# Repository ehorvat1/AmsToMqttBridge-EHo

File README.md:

# AMS2MQTTBridge-EHo
This is basically a fork from amsreader-firmware (old name: AmsToMqttBridge) amsreader-firmware based on Rev 2.2.21 from here: (https://github.com/UtilitechAS/amsreader-firmware)

Because of memory limitations for ESP8266 which made OTA firmware update impossible I had to delete the automatic firmware detection/download/consent. So this firmware can only be updated via status web page (Upload Firmware) or by using direct serial connection to ESP device.

Now features:
1) All functions from amsreader-firmware Rev 2.2.21 (Except automatic FW updates which would overwrite my modifications)
2) Fixed price (but its more a refund) for exported energy 
3) Added a 10 Minute plot (120 point resolution, 1 pt each 5 sec)
4) Added a 60 Minute plot (120 point resolution, 1 pt each 30 sec)
5) Added a section to show "last" counter values since last payment. Data to be entered in configuration.
6) Exported energy is shown in green color on hour, day and month plot.
7) Automatic Wifi swapping if configured WLAN does not connect. See below for more info.
8) Disabled Consent message (since no data is sent anywhere) and automatic FW updates
9) Some minor color changes on dashboard gauges

There is a German Version as well, please go to "main" branch or to the Release version ending with "-ge" . Link: https://github.com/ehorvat1/AmsToMqttBridge-EHo/tree/main

## Wifi function (STA mode or AP mode):
The option on configuration page in section Wifi called:  "Start a Wifi AP on home Wifi connection problem" will enable this:
If the configured Wifi (should be your home Wifi) can not be reached within app. 2 minutes software will swap to Wifi AP mode and will present a AP named "amsreader-abcd" with **password: amsreader_config** so one can acess the web pages on its default IP: 192.168.4.1

Software will try to re-connect to the configured Wifi if no client is connected to this AP for 90 seconds. So if one is connected to AP Wifi the device will stay in AP mode. Please mind that most devices will do a automatic reconnect to the AP Wifi if the Wifi connection "amsreader-abcd" was once used. This could prevent the ESP32 from automatically reconnecting to defined STA Wifi.

"AP" button still is an option to swap between configured WLAN and an Wifi Access point called "amsreader-abcd". The AP button must be pressed longer than 5 seconds to swap Wifi mode.

## Additional MQTT items (in raw MQTT mode only):
	 - Publish topic + "/realtime/import/cost_kwh"
	 - Publish topic + "/realtime/import/last_counter_value"
	 - Publish topic + "/realtime/import/last_counter_info"
	 - Publish topic + "/realtime/import/last_counter_diff"
	 - Publish topic + "/realtime/import/last_counter_costs"
	 - Publish topic + "/realtime/export/refund_kwh"
	 - Publish topic + "/realtime/export/last_counter_value"
	 - Publish topic + "/realtime/export/last_counter_info"
	 - Publish topic + "/realtime/export/last_counter_diff"
	 - Publish topic + "/realtime/export/last_counter_refund"

So for example, if you set the "Publish topic" in MQTT configuration to "smartmeter" :
          -the actual power used is published with full topic: smartmeter/meter/import/active
          -the entered fixed price per kWh is published with full topic: smartmeter/realtime/import/cost_kwh
	  
## Dashboard website:

## Original README.md from amsreader-firmware:

This code is designed to decode data from electric smart meters installed in many countries in Europe these days. The data is presented in a graphical web interface and can also send the data to a MQTT broker which makes it suitable for home automation project. Originally it was only designed to work with Norwegian meters, but has since been adapter to read any IEC-62056-7-5 or IEC-62056-21 compliant meters.

Later development have added Energy usage graph for both day and month, as well as future energy price (Prices only  available for ESP32). The code can run on any ESP8266 or ESP32 hardware which you can read more about in the [WiKi](https://github.com/gskjold/AmsToMqttBridge/wiki). If you don't have the knowledge to set up a ESP device yourself, have a look at the shop at [amsleser.no](https://amsleser.no/).

Go to the [WiKi](https://github.com/gskjold/AmsToMqttBridge/wiki) for information on how to get your own device! And find the latest prebuilt firmware file at the [release section](https://github.com/gskjold/AmsToMqttBridge/releases).

## Building this project with PlatformIO
To build this project, you need [PlatformIO](https://platformio.org/) installed.

It is recommended to use Visual Studio Code with the PlatformIO plugin for development.

[Visual Studio Code](https://code.visualstudio.com/download)

[PlatformIO vscode plugin](https://platformio.org/install/ide?install=vscode)

For development purposes, copy the ```platformio-user.ini-example``` to ```platformio-user.ini``` and customize to your preference. The code will adapt to the platform and board set in your profile.

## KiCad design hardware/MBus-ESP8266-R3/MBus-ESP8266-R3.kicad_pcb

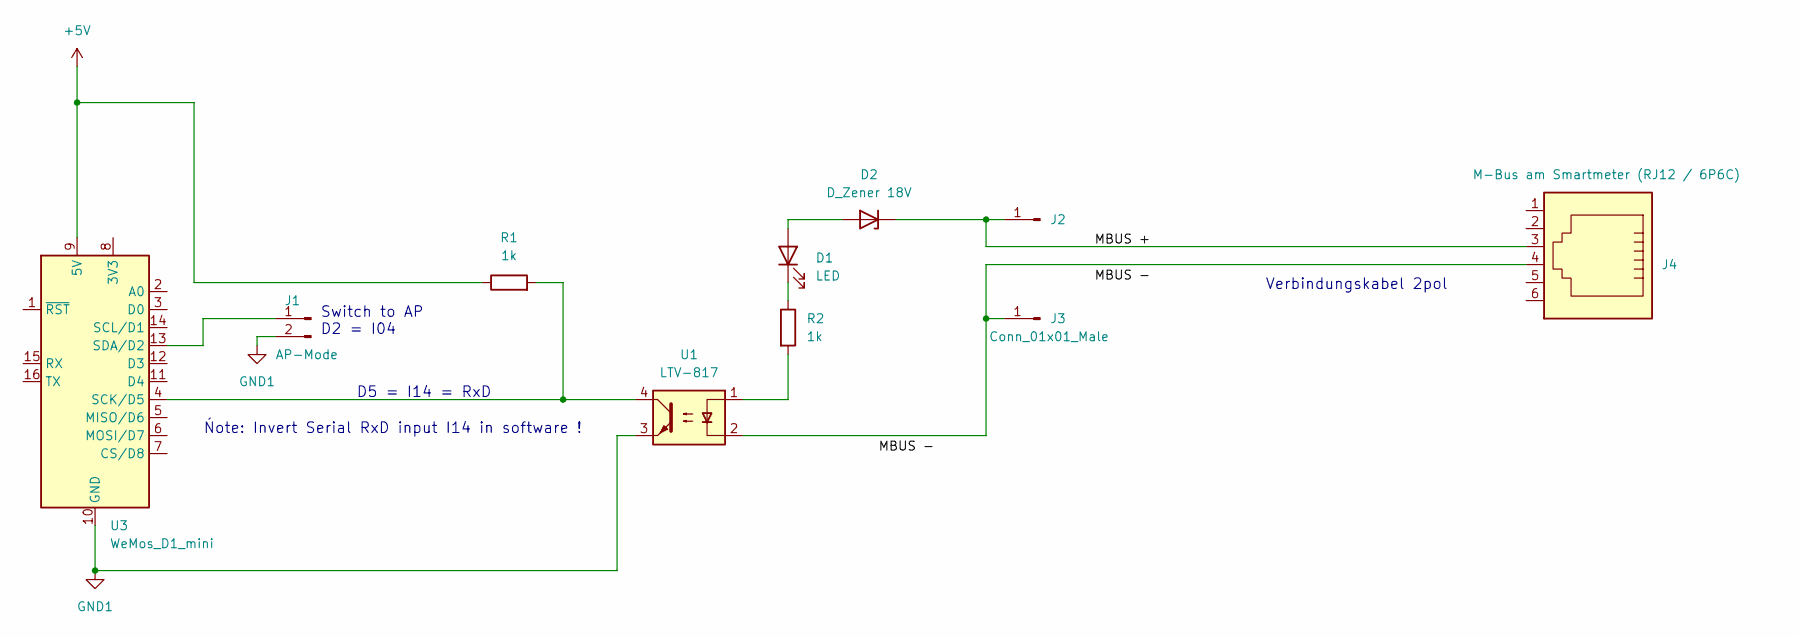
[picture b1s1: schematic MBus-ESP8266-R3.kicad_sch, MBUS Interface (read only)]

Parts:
D1: LED; LED_D3.0mm
D2: D_Zener 18V; D_A-405_P10.16mm_Horizontal
J1: AP-Mode; PinHeader_1x02_P2.54mm_Vertical
J2, J3: Conn_01x01_Male; Pin_D1.0mm_L10.0mm
J4: M-Bus am Smartmeter (RJ12 / 6P6C); RJ12_Amphenol_54601
R1, R2: 1k; R_Axial_DIN0207_L6.3mm_D2.5mm_P10.16mm_Horizontal
U1: LTV-817; DIP-4_W7.62mm
U3: WeMos_D1_mini; WEMOS_D1_mini_light

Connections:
+5V: R1.1, U3.9 (5V)
/MBUS +: D2.1 (K), J2.1, J4.3
GND1: J1.2, U1.3, U3.10 (GND)
unnamed: D1.2 (A), D2.2 (A)
unnamed: D1.1 (K), R2.1
unnamed: J1.1, U3.13 (SDA/D2)
unnamed: J3.1, J4.4, U1.2
unnamed: R2.2, U1.1
unnamed: R1.2, U1.4, U3.4 (SCK/D5)

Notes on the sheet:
D5 = I14 = RxD
Switch to AP D2 = I04
Ńote: Invert Serial RxD input I14 in software !
Verbindungskabel 2pol

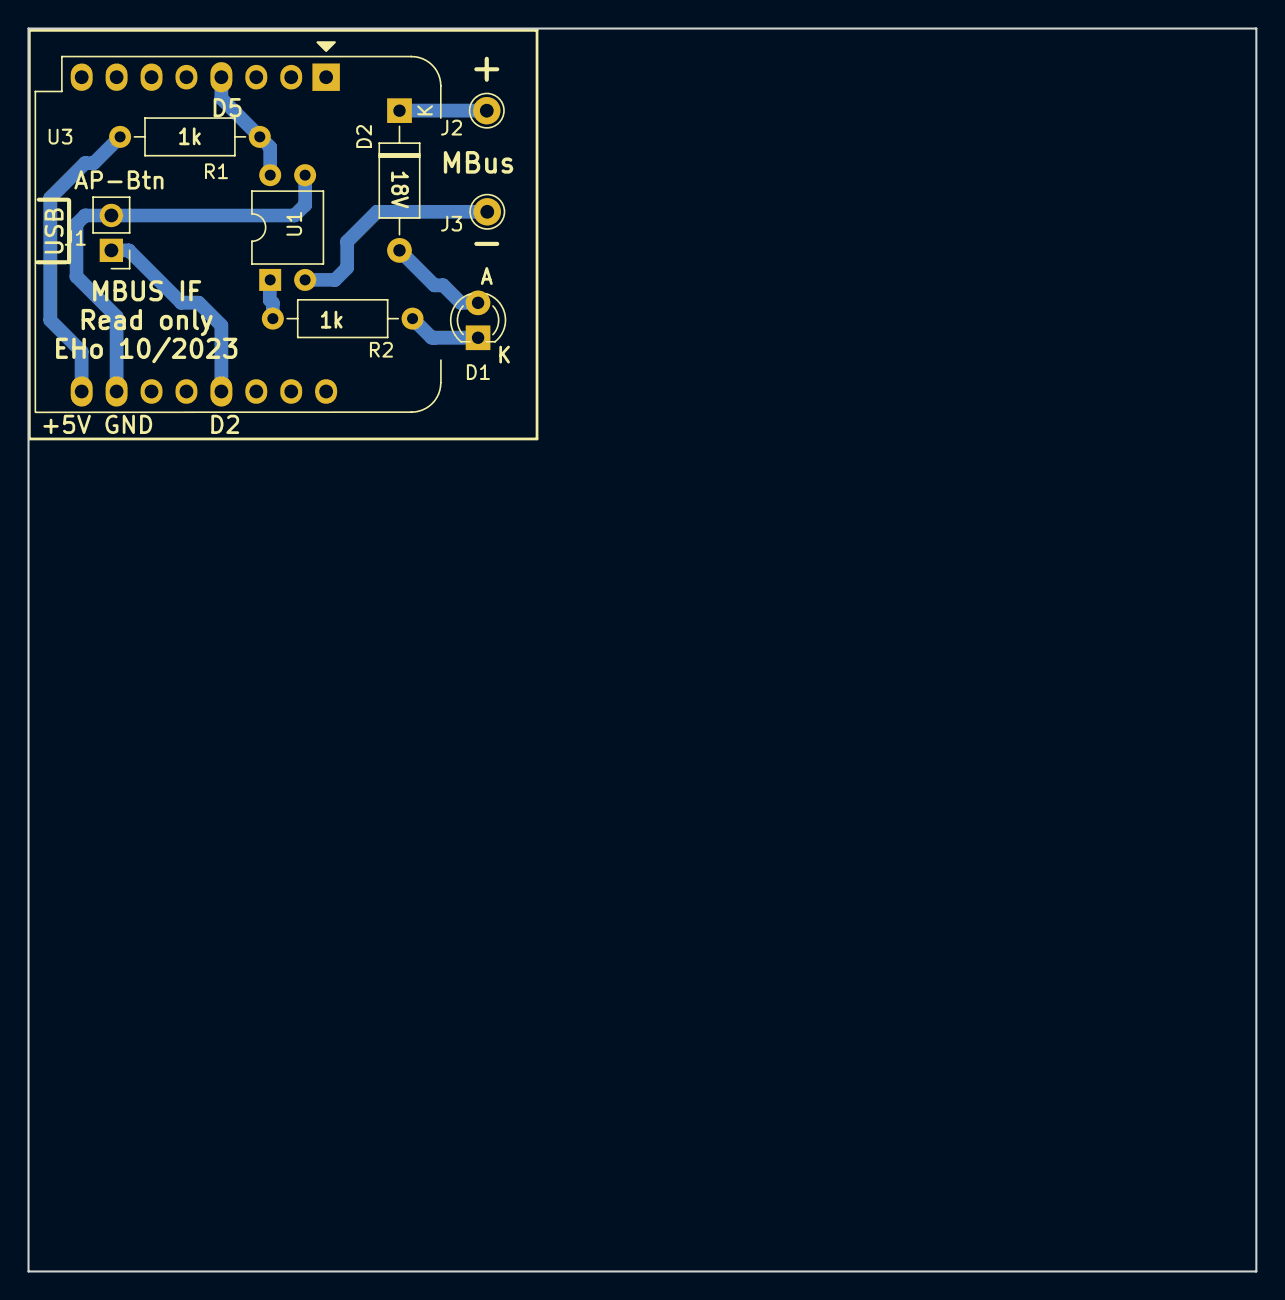
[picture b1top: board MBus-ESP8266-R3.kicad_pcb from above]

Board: 2 copper layers, 89.3 x 90.4 mm, 9 parts (0 on the bottom side), 9 nets.

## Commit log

2024-01-16 Serial buffer size fixed to 128 Bytes
    Serial buffer size fixed to 128 Bytes. Also disabled automatic increase of buffer size
2024-01-16 Measurements on Sagecom Smartmeter from EVN added
2024-01-17 Serial buffer size fixed to 128 Bytes
    Serial buffer size fixed to 128 Bytes and Debugging level changed to see when valid frame occured
2024-01-17 Serial buffer size fixed to 128 Bytes
    Serial buffer size fixed to 128 Bytes and debugging level changed to see valid DLMS frames arriving
